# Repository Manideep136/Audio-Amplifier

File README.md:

# Audio Amplifier 

A custom Audio Amplifier PCB designed using KiCad.

## Overview

This project contains the schematic and PCB design for an audio amplifier
circuit. The PCB includes an audio input, volume control, amplifier section,
power connections, and audio output.

The complete board was designed using KiCad, including schematic capture,
component footprints, PCB routing, and 3D visualization.

## Features

- Audio input through audio jack
- Volume control using potentiometer
- Audio amplification circuit
- Power supply connection
- Audio output connection
- Custom PCB layout
- KiCad schematic and PCB files
- 3D PCB visualization

## Software

- KiCad
- KiCad Schematic Editor
- KiCad PCB Editor
- KiCad 3D Viewer

## Components

The project includes components such as:

- Audio Jack
- Potentiometer
- Amplifier IC
- Resistors
- Capacitors
- Power connector
- Audio output connector

## Audio Input

The audio input uses a 3.5 mm audio jack.

The jack provides:

- Tip – Audio signal
- Ring – Additional audio contact
- Sleeve – Ground/reference

The Ring connection is left unused in this design and is marked as
**No Connect** in the KiCad schematic.

## PCB Design Process

The PCB was developed using the following steps:

1. Create the circuit schematic.
2. Assign footprints to the components.
3. Add 3D models where required.
4. Transfer the schematic to the PCB Editor.
5. Place the components.
6. Route the PCB tracks.
7. Check the PCB layout.
8. Run the Design Rules Check (DRC).
9. View the completed PCB using the KiCad 3D Viewer.

## Project Files

```text
Audio Amplifier/
│
├── Audio Amplifier.kicad_pro
├── Audio Amplifier.kicad_sch
├── Audio Amplifier.kicad_pcb
└── README.md

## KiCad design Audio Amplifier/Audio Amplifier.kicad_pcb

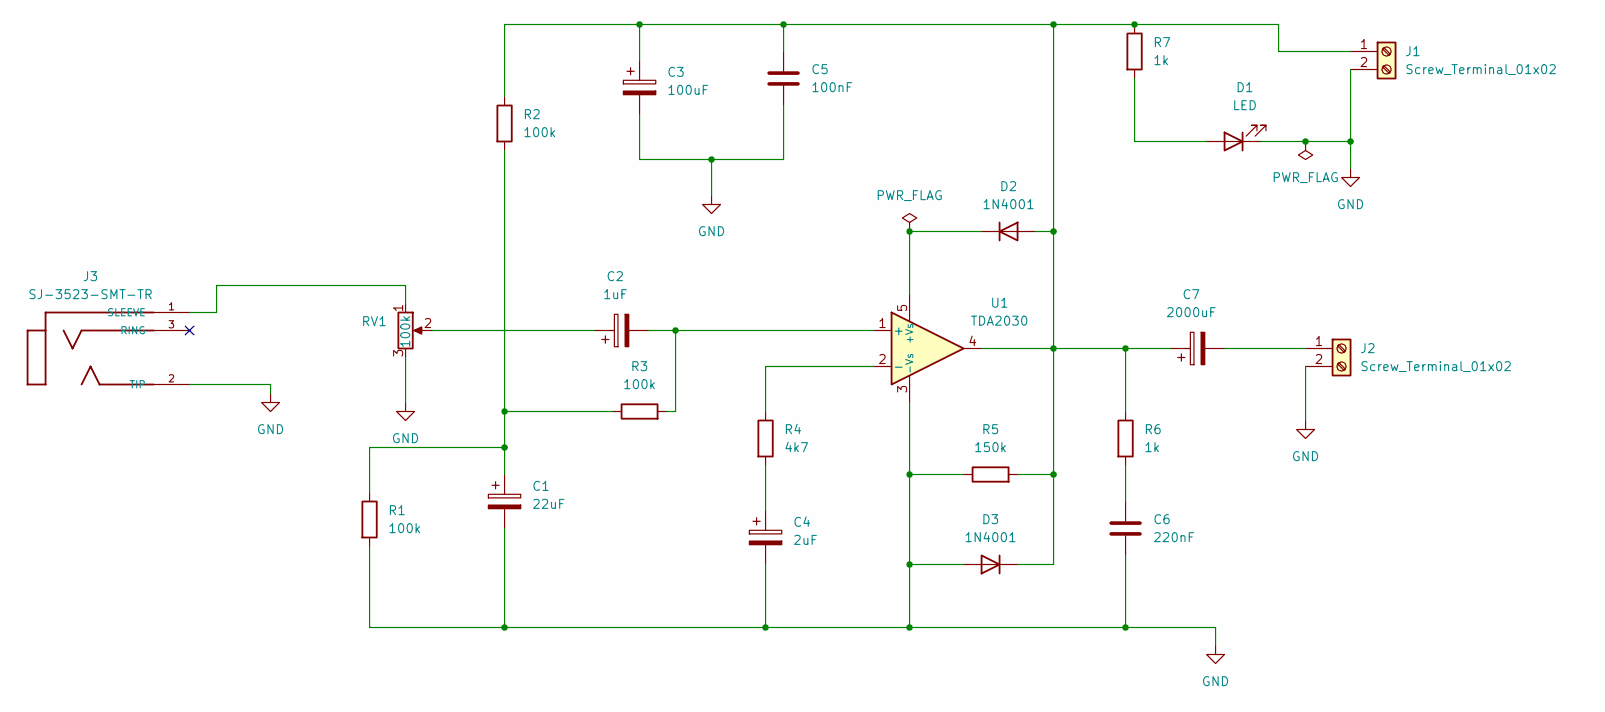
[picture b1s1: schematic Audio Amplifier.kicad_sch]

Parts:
C1: 22uF; C_Radial_D5.0mm_H5.0mm_P2.00mm
C2: 1uF; C_Radial_D5.0mm_H5.0mm_P2.00mm
C3: 100uF; C_Radial_D6.3mm_H7.0mm_P2.50mm
C4: 2uF; C_Radial_D5.0mm_H5.0mm_P2.00mm
C5: 100nF; C_Disc_D3.8mm_W2.6mm_P2.50mm
C6: 220nF; C_Disc_D3.8mm_W2.6mm_P2.50mm
C7: 2000uF; C_Radial_D10.0mm_H16.0mm_P5.00mm
D1: LED; LED_D5.0mm
D2, D3: 1N4001; D_DO-41_SOD81_P10.16mm_Horizontal
J1, J2: Screw_Terminal_01x02; TerminalBlock_Phoenix_MKDS-1,5-2-5.08_1x02_P5.08mm_Horizont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
J3: SJ-3523-SMT-TR; CUI_SJ-3523-SMT-TR
R1, R2, R3: 100k; R_Axial_DIN0207_L6.3mm_D2.5mm_P7.62mm_Horizontal
R4: 4k7; R_Axial_DIN0207_L6.3mm_D2.5mm_P7.62mm_Horizontal
R5: 150k; R_Axial_DIN0207_L6.3mm_D2.5mm_P7.62mm_Horizontal
R6, R7: 1k; R_Axial_DIN0207_L6.3mm_D2.5mm_P7.62mm_Horizontal
RV1: 100k; Potentiometer_Piher_PC-16_Single_Horizontal
U1: TDA2030; TO-220-5_P3.4x3.7mm_StaggerOdd_Lead3.8mm_Vertical

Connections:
GND: C1.2, C3.2, C4.2, C5.2, C6.2, D1.1 (K), D3.2 (A), J1.2, J2.2, J3.2 (TIP), R1.2, R5.1, RV1.3, U1.3 (-Vs)
unnamed: C1.1, R1.1, R2.2, R3.1
unnamed: C2.1, RV1.2
unnamed: C4.1, R4.2
unnamed: C6.1, R6.2
unnamed: D1.2 (A), R7.2
unnamed: C3.1, C5.1, C7.1, D2.2 (A), D3.1 (K), J1.1, R2.1, R5.2, R6.1, R7.1, U1.4
unnamed: D2.1 (K), U1.5 (+Vs)
unnamed: C7.2, J2.1
unnamed: J3.1 (SLEEVE), RV1.1
unnamed: C2.2, R3.2, U1.1 (+)
unnamed: R4.1, U1.2 (-)

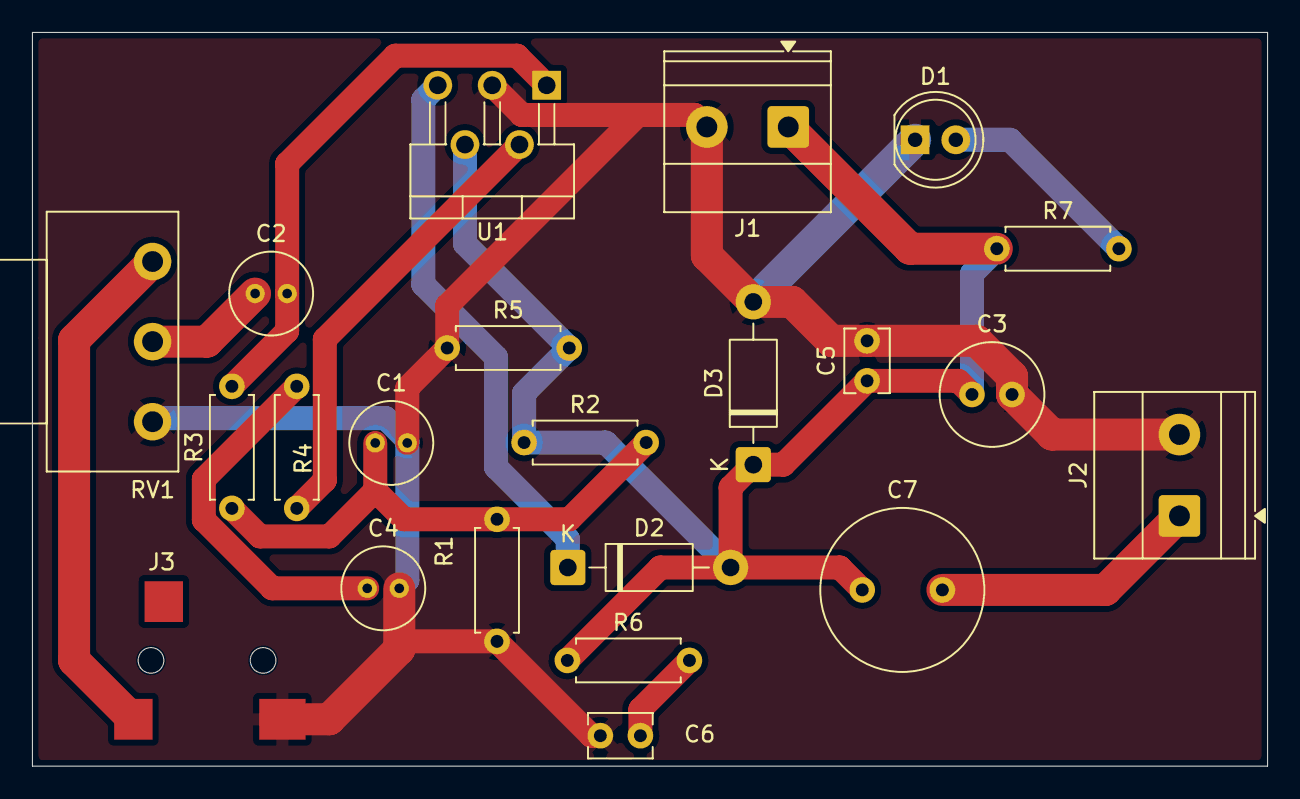
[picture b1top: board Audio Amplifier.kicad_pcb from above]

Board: 2 copper layers, 77.1 x 45.8 mm, 22 parts (0 on the bottom side), 12 nets.
